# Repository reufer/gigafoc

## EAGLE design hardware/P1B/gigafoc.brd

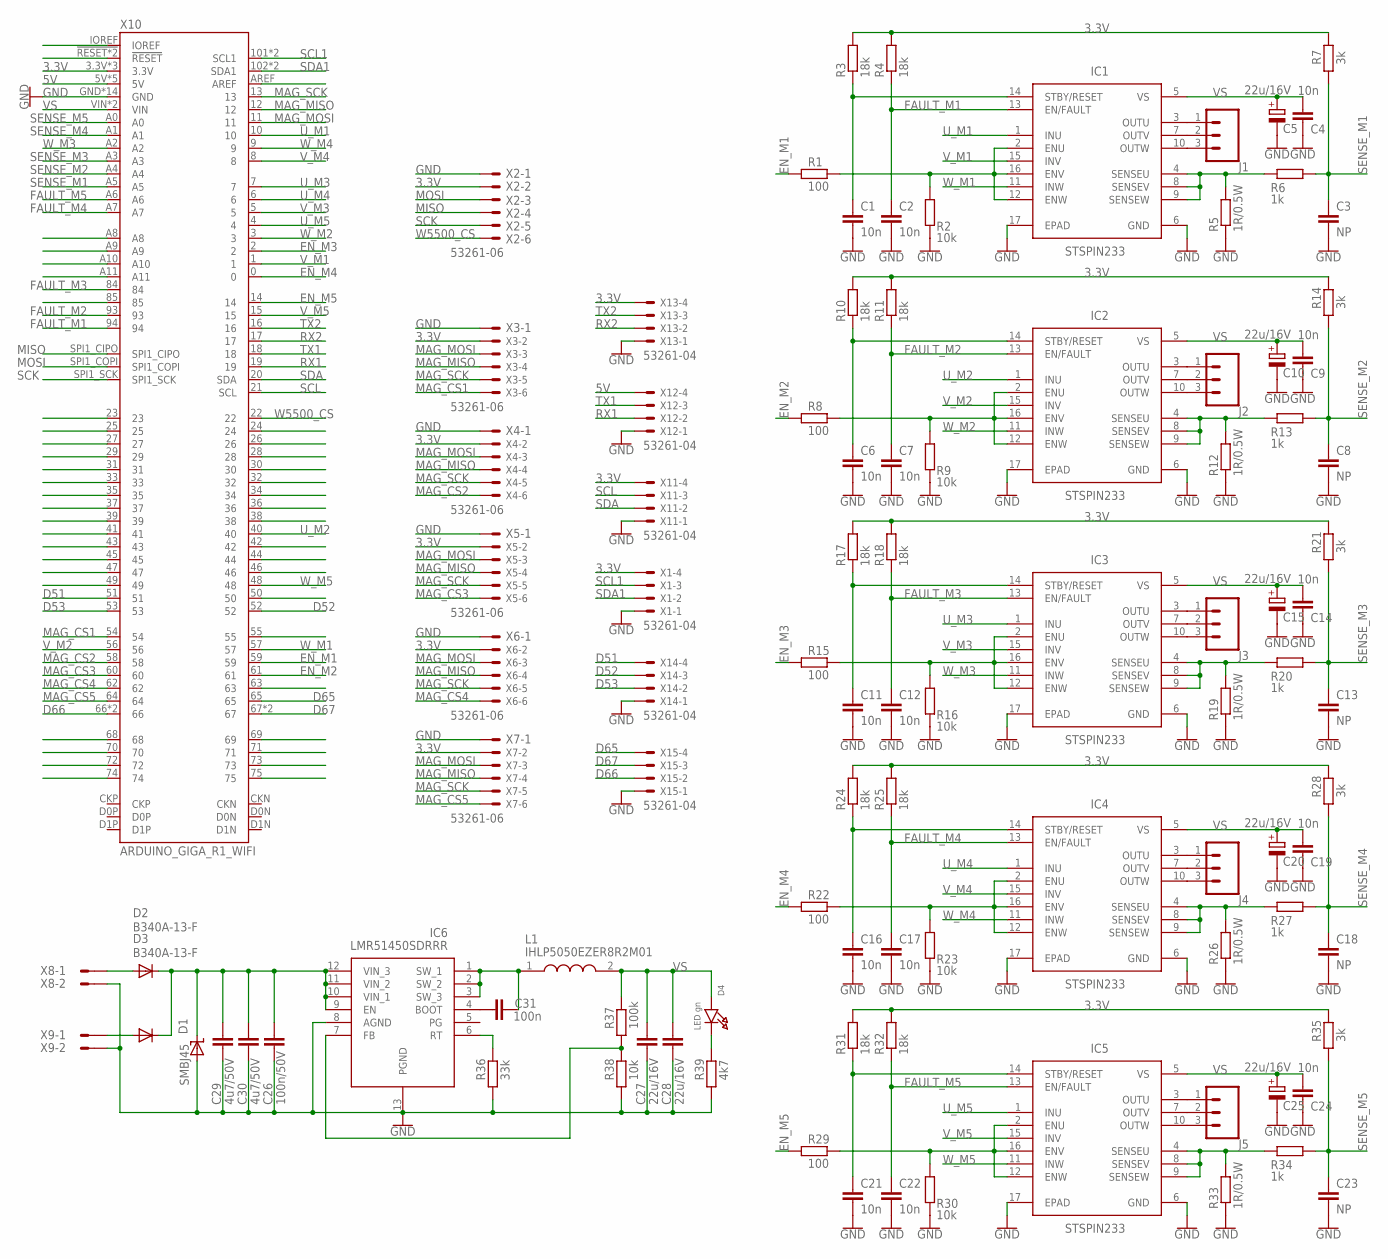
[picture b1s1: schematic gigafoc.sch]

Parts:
C1, C2, C4, C6, C7, C9, C11, C12, C14, C16, C17, C19, C21, C22, C24: 10n; C0603
C3, C8, C13, C18, C23: NP; C0603
C5, C10, C15, C20, C25: 22u/16V; SMC_B
C26: 100n/50V; C0805
C27, C28: 22u/16V; C1210
C29, C30: 4u7/50V; C1210K
C31: 100n; C0603
D1: SMBJ45; SMBJ
D2, D3: B340A-13-F; DO214AC
D4: LED gn; CHIPLED_0603_NOOUTLINE
IC1, IC2, IC3, IC4, IC5: STSPIN233; QFN50P300X300X100-17N
IC6: LMR51450SDRRR; SON50P300X300X80-13N
J1, J2, J3, J4, J5: CONN_03POLAR; MOLEX-1X3
L1: IHLP5050EZER8R2M01; INDPM132129X500N
R1, R8, R15, R22, R29: 100; R0603
R2, R9, R16, R23, R30, R38: 10k; R0603
R3, R4, R10, R11, R17, R18, R24, R25, R31, R32: 18k; R0603
R5, R12, R19, R26, R33: 1R/0.5W; R1206
R6, R13, R20, R27, R34: 1k; R0603
R7, R14, R21, R28, R35: 3k; R0603
R36: 33k; R0603
R37: 100k; R0603
R39: 4k7; R0603
X1, X11, X12, X13, X14, X15: 53261-04
X2, X3, X4, X5, X6, X7: 53261-06
X8, X9: S02P
X10: ARDUINO_GIGA_R1_WIFI; ARDUINO_GIGA_NO_SILK

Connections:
3.3V: R3.2, R4.2, R7.2, R10.2, R11.2, R14.2, R17.2, R18.2, R21.2, R24.2, R25.2, R28.2, R31.2, R32.2, R35.2, X1.4, X2.2, X3.2, X4.2, X5.2, X6.2, X7.2, X10.3.3V, X10.3.3V@1 (3.3V), X10.3.3V@2 (3.3V), X11.4, X13.4
5V: X10.5V, X10.5V@1 (5V), X10.5V@2 (5V), X10.5V@3 (5V), X10.5V@4 (5V), X12.4
24V: D2.A, X8.1
D51: X10.51, X14.4
D52: X10.52, X14.3
D53: X10.53, X14.2
D65: X10.65, X15.4
D66: X10.66, X10.66@1 (66), X15.2
D67: X10.67, X10.67@1 (67), X15.3
EN_M1: R1.1, X10.59
EN_M2: R8.1, X10.61
EN_M3: R15.1, X10.2
EN_M4: R22.1, X10.0
EN_M5: R29.1, X10.14
FAULT_M1: C2.2, IC1.13 (EN/FAULT), R4.1, X10.94
FAULT_M2: C7.2, IC2.13 (EN/FAULT), R11.1, X10.93
FAULT_M3: C12.2, IC3.13 (EN/FAULT), R18.1, X10.84
FAULT_M4: C17.2, IC4.13 (EN/FAULT), R25.1, X10.A7
FAULT_M5: C22.2, IC5.13 (EN/FAULT), R32.1, X10.A6
GND: C1.1, C2.1, C3.1, C4.1, C5.-, C6.1, C7.1, C8.1, C9.1, C10.-, C11.1, C12.1, C13.1, C14.1, C15.-, C16.1, C17.1, C18.1, C19.1, C20.-, C21.1, C22.1, C23.1, C24.1, C25.-, C26.2, C27.2, C28.2, C29.2, C30.2, D1.A, IC1.6 (GND), IC1.17 (EPAD), IC2.6 (GND), IC2.17 (EPAD), IC3.6 (GND), IC3.17 (EPAD), IC4.6 (GND), IC4.17 (EPAD), IC5.6 (GND), IC5.17 (EPAD), IC6.8 (AGND), IC6.13 (PGND), R2.1, R5.1, R9.1, R12.1, R16.1, R19.1, R23.1, R26.1, R30.1, R33.1, R36.1, R38.1, R39.1, X1.1, X2.1, X3.1, X4.1, X5.1, X6.1, X7.1, X8.2, X9.2, X10.GND, X10.GND@1 (GND), X10.GND@2 (GND), X10.GND@3 (GND), X10.GND@4 (GND), X10.GND@5 (GND), X10.GND@6 (GND), X10.GND@7 (GND), X10.GND@8 (GND), X10.GND@9 (GND), X10.GND@10 (GND), X10.GND@11 (GND), X10.GND@12 (GND), X10.GND@13 (GND), X11.1, X12.1, X13.1, X14.1, X15.1
MAG_CS1: X3.6, X10.54
MAG_CS2: X4.6, X10.58
MAG_CS3: X5.6, X10.60
MAG_CS4: X6.6, X10.62
MAG_CS5: X7.6, X10.64
MAG_MISO: X3.4, X4.4, X5.4, X6.4, X7.4, X10.12
MAG_MOSI: X3.3, X4.3, X5.3, X6.3, X7.3, X10.11
MAG_SCK: X3.5, X4.5, X5.5, X6.5, X7.5, X10.13
MISO: X2.4, X10.SPI1_CIPO
MOSI: X2.3, X10.SPI1_COPI
unnamed: IC1.2 (ENU), IC1.12 (ENW), IC1.16 (ENV), R1.2, R2.2
unnamed: C1.2, IC1.14 (STBY/RESET), R3.1
unnamed: IC1.4 (SENSEU), IC1.8 (SENSEV), IC1.9 (SENSEW), R5.2, R6.1
unnamed: C31.1, IC6.4 (BOOT)
unnamed: C31.2, IC6.1 (SW_1), IC6.2 (SW_2), IC6.3 (SW_3), L1.1
unnamed: IC1.3 (OUTU), J1.1
unnamed: IC1.7 (OUTV), J1.2
unnamed: IC1.10 (OUTW), J1.3
unnamed: D4.C, R39.2
unnamed: D3.A, X9.1
unnamed: IC6.7 (FB), R37.1, R38.2
unnamed: IC6.6 (RT), R36.2
unnamed: IC2.2 (ENU), IC2.12 (ENW), IC2.16 (ENV), R8.2, R9.2
unnamed: C6.2, IC2.14 (STBY/RESET), R10.1
unnamed: IC2.4 (SENSEU), IC2.8 (SENSEV), IC2.9 (SENSEW), R12.2, R13.1
unnamed: IC2.3 (OUTU), J2.1
unnamed: IC2.7 (OUTV), J2.2
unnamed: IC2.10 (OUTW), J2.3
unnamed: IC3.2 (ENU), IC3.12 (ENW), IC3.16 (ENV), R15.2, R16.2
unnamed: C11.2, IC3.14 (STBY/RESET), R17.1
unnamed: IC3.4 (SENSEU), IC3.8 (SENSEV), IC3.9 (SENSEW), R19.2, R20.1
unnamed: X10.!RESET, X10.RESET (!RESET)
unnamed: IC3.3 (OUTU), J3.1
unnamed: IC3.7 (OUTV), J3.2
unnamed: IC3.10 (OUTW), J3.3
unnamed: IC4.2 (ENU), IC4.12 (ENW), IC4.16 (ENV), R22.2, R23.2
unnamed: C16.2, IC4.14 (STBY/RESET), R24.1
unnamed: IC4.4 (SENSEU), IC4.8 (SENSEV), IC4.9 (SENSEW), R26.2, R27.1
unnamed: IC4.3 (OUTU), J4.1
unnamed: IC4.7 (OUTV), J4.2
unnamed: IC4.10 (OUTW), J4.3
unnamed: IC5.2 (ENU), IC5.12 (ENW), IC5.16 (ENV), R29.2, R30.2
unnamed: C21.2, IC5.14 (STBY/RESET), R31.1
unnamed: IC5.4 (SENSEU), IC5.8 (SENSEV), IC5.9 (SENSEW), R33.2, R34.1
unnamed: IC5.3 (OUTU), J5.1
unnamed: IC5.7 (OUTV), J5.2
unnamed: IC5.10 (OUTW), J5.3
RX1: X10.19, X12.2
RX2: X10.17, X13.2
SCK: X2.5, X10.SPI1_SCK
SCL: X10.21 (SCL), X11.3
SCL1: X1.3, X10.101 (SCL1), X10.101@1 (SCL1)
SDA: X10.20 (SDA), X11.2
SDA1: X1.2, X10.102 (SDA1), X10.102@1 (SDA1)
SENSE_M1: C3.2, R6.2, R7.1, X10.A5
SENSE_M2: C8.2, R13.2, R14.1, X10.A4
SENSE_M3: C13.2, R20.2, R21.1, X10.A3
SENSE_M4: C18.2, R27.2, R28.1, X10.A1
SENSE_M5: C23.2, R34.2, R35.1, X10.A0
TX1: X10.18, X12.3
TX2: X10.16, X13.3
U_M1: IC1.1 (INU), X10.10
U_M2: IC2.1 (INU), X10.40
U_M3: IC3.1 (INU), X10.7
U_M4: IC4.1 (INU), X10.6
U_M5: IC5.1 (INU), X10.4
VIN: C26.1, C29.1, C30.1, D1.C, D2.C, D3.C, IC6.9 (EN), IC6.10 (VIN_1), IC6.11 (VIN_2), IC6.12 (VIN_3)
VS: C4.2, C5.+, C9.2, C10.+, C14.2, C15.+, C19.2, C20.+, C24.2, C25.+, C27.1, C28.1, D4.A, IC1.5 (VS), IC2.5 (VS), IC3.5 (VS), IC4.5 (VS), IC5.5 (VS), L1.2, R37.2, X10.VIN, X10.VIN@1 (VIN)
V_M1: IC1.15 (INV), X10.1
V_M2: IC2.15 (INV), X10.56
V_M3: IC3.15 (INV), X10.5
V_M4: IC4.15 (INV), X10.8
V_M5: IC5.15 (INV), X10.15
W5500_CS: X2.6, X10.22
W_M1: IC1.11 (INW), X10.57
W_M2: IC2.11 (INW), X10.3
W_M3: IC3.11 (INW), X10.A2
W_M4: IC4.11 (INW), X10.9
W_M5: IC5.11 (INW), X10.48

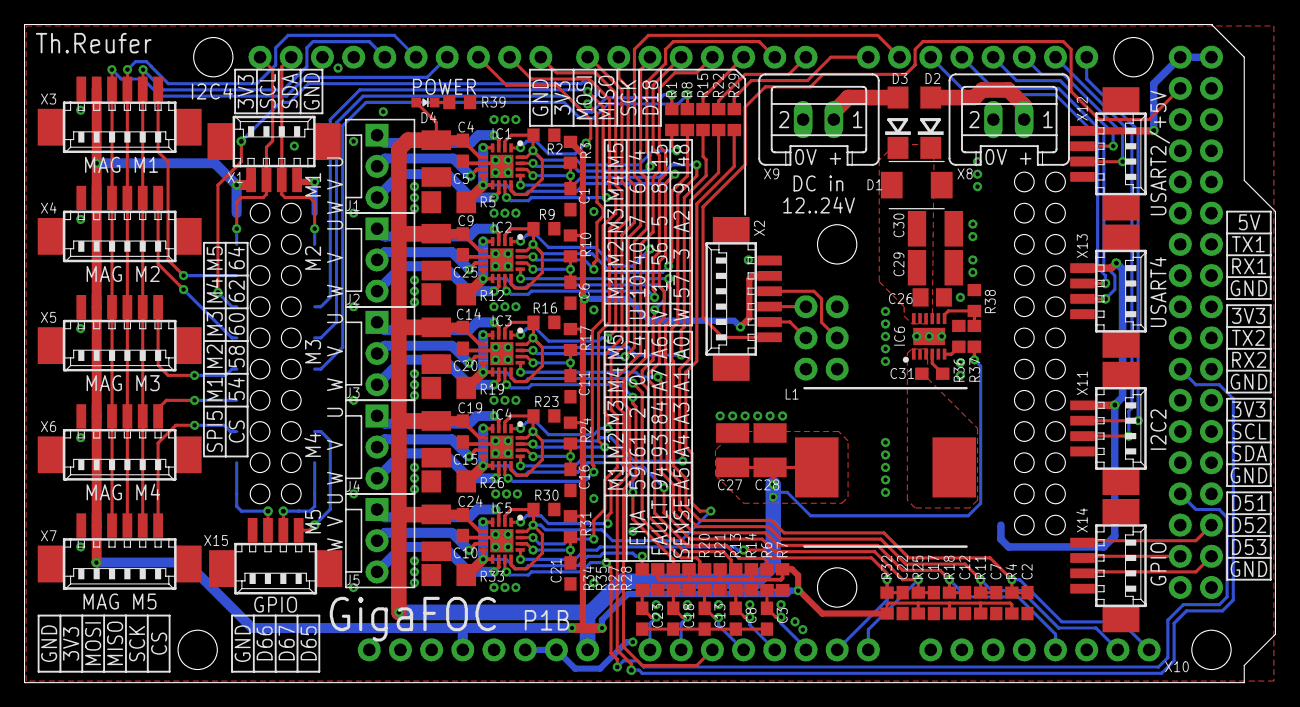
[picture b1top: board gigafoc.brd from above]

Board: 2 copper layers, 101.9 x 53.6 mm, 101 parts (0 on the bottom side), 99 nets.

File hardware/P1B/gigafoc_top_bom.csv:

Comment,Designator,Footprint,LCSC Part #
1R/0.5W,R5 R12 R19 R26 R33,R1206,C880596
3k,R7 R14 R21 R28 R35,R0603,C4211
4k7,R39,R0603,C23162
4u7/50V,C29 C30,C1210K,C880822
10k,R2 R9 R16 R23 R30 R38,R0603,C25804
10n,C1 C2 C4 C6 C7 C9 C11 C12 C14 C16 C17 C19 C21 C22 C24,C0603,C57112
18k,R3 R4 R10 R11 R17 R18 R24 R25 R31 R32,R0603,C25810
22u/16V,C5 C10 C15 C20 C25,SMC_B,C55530
22u/16V,C27 C28,C1210,C2180585
33k,R36,R0603,C4216
100,R1 R8 R15 R22 R29,R0603,C5123610
100k,R37,R0603,C25803
100n,C31,C0603,C57112
100n/50V,C26,C0805,C710626
1k,R6 R13 R20 R27 R34,R0603,C21190
53261-04,X1 X11 X12 X13 X14 X15,53261-04,C696092
53261-06,X2 X3 X4 X5 X6 X7,53261-06,C17393620
B340A-13-F,D2 D3,DO214AC,C85098
IHLP5050EZER8R2M01,L1,INDPM132129X500N,C845094
LED gn,D4,CHIPLED_0603_NOOUTLINE,C12624
LMR51450SDRRR,IC6,SON50P300X300X80-13N,C6890985
SMBJ45,D1,SMBJ,C440304
STSPIN233,IC1 IC2 IC3 IC4 IC5,QFN50P300X300X100-17N,C2653468

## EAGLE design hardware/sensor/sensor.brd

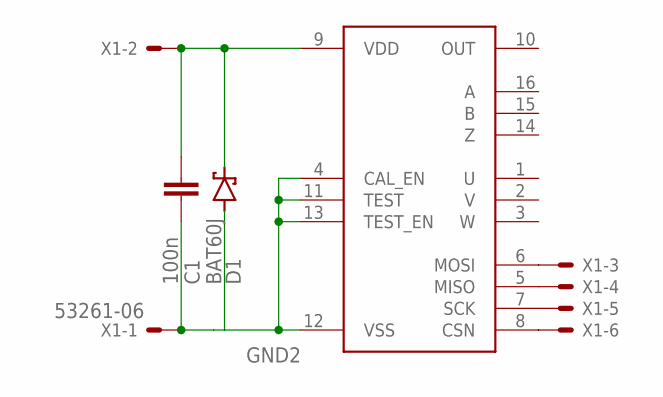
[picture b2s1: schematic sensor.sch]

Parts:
C1: 100n; C0603
D1: BAT60J; SOD323_ST
IC1: MT6835; TSSOP-16
X1: 53261-06

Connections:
GND2: C1.2, D1.A, IC1.4 (CAL_EN), IC1.11 (TEST), IC1.12 (VSS), IC1.13 (TEST_EN), X1.1
unnamed: IC1.5 (MISO), X1.4
unnamed: IC1.7 (SCK), X1.5
unnamed: IC1.8 (CSN), X1.6
unnamed: IC1.6 (MOSI), X1.3
unnamed: C1.1, D1.C, IC1.9 (VDD), X1.2

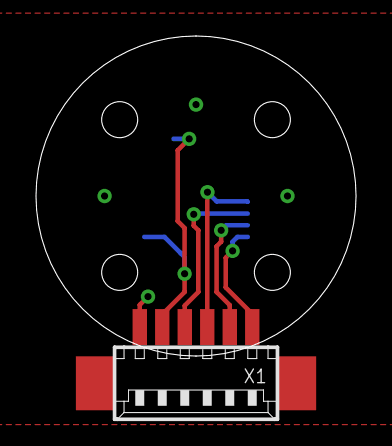
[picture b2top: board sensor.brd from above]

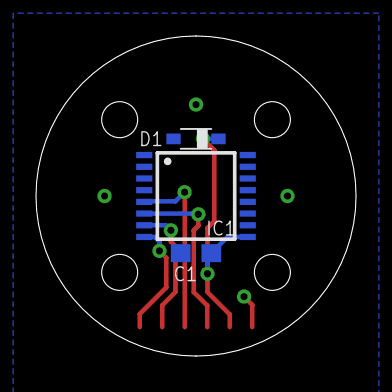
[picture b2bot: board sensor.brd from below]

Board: 2 copper layers, 17.8 x 17.8 mm, 4 parts (3 on the bottom side), 6 nets.

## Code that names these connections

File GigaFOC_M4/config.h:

#pragma once

#include <PinNames.h>

#define HARDWARE_P1A
//#define HARDWARE_P1B

#define MOTOR_2204

//#define SENSOR_MT6701
#define SENSOR_MT6835

#define DRIVER_MBED
//#define DRIVER_PORTENTA
//#define DRIVER_STM32

#define MOTORS 5

#define MOTOR_PP 7
#define MOTOR_KV NOT_SET
#define MOTOR_L NOT_SET
#define MOTOR_R NOT_SET

#ifdef MOTOR_2204
#define MOTOR_PP 7
#define MOTOR_KV 260.0f
#define MOTOR_L 0.00173f
#define MOTOR_R 10.0f
#endif

#define VOLTAGE_POWER_SUPPLY 9
#define VOLTAGE_SENSOR_ALIGN 3
#define VELOCITY_INDEX_SEARCH 3

// Hardware P1A
#ifdef HARDWARE_P1A
#define PIN_U_M1    D10 // PK1_ALT1
#define PIN_V_M1    D1  // PA9_ALT1
#define PIN_W_M1    D57 // PJ9_ALT1

#define PIN_U_M2    D85 // PA5
#define PIN_V_M2    D66 // PA1
#define PIN_W_M2    D3  // PA2

#define PIN_U_M3    D7  // PB4
#define PIN_V_M3    D5  // PA7_ALT1
#define PIN_W_M3    A2  // PB0_ALT1

#define PIN_U_M4    D6  // PD13
#define PIN_V_M4    D8  // PB8
#define PIN_W_M4    D9  // PB9

#define PIN_U_M5    D4  // PJ8_ALT1
#define PIN_V_M5    D15 // PC7_ALT1
#define PIN_W_M5    D48 // PK0_ALT1

#define PIN_EN_M1   D2
#define PIN_EN_M2   D14
#define PIN_EN_M3   D0
#define PIN_EN_M4   D16
#define PIN_EN_M5   D17

#define PIN_MAG_CS1 D56
#define PIN_MAG_CS2 D58
#define PIN_MAG_CS3 D60
#define PIN_MAG_CS4 D62
#define PIN_MAG_CS5 D64

#define PIN_SENSE_M1 A5
#define PIN_SENSE_M2 A4
#define PIN_SENSE_M3 A3
#define PIN_SENSE_M4 A1
#define PIN_SENSE_M5 A0

#define PIN_FAULT_M1 D94
#define PIN_FAULT_M2 D93
#define PIN_FAULT_M3 D84
#define PIN_FAULT_M4 A7
#define PIN_FAULT_M5 A6
#endif

// Hardware P1B
#ifdef HARDWARE_P1B
#define PIN_U_M1    D10 // PK1_ALT1
#define PIN_V_M1    D1  // PA9_ALT1
#define PIN_W_M1    D57 // PJ9_ALT1

#define PIN_U_M2    D40 // PE6
#define PIN_V_M2    D56 // PA6
#define PIN_W_M2    D3  // PA2

#define PIN_U_M3    D7  // PB4
#define PIN_V_M3    D5  // PA7_ALT1
#define PIN_W_M3    A2  // PB0_ALT1

#define PIN_U_M4    D6  // PD13
#define PIN_V_M4    D8  // PB8
#define PIN_W_M4    D9  // PB9

#define PIN_U_M5    D4  // PJ8_ALT1
#define PIN_V_M5    D15 // PC7_ALT1
#define PIN_W_M5    D48 // PK0_ALT1

#define PIN_EN_M1   D59
#define PIN_EN_M2   D61
#define PIN_EN_M3   D2
#define PIN_EN_M4   D0
#define PIN_EN_M5   D14

#define PIN_MAG_CS1 D54
#define PIN_MAG_CS2 D58
#define PIN_MAG_CS3 D60
#define PIN_MAG_CS4 D62
#define PIN_MAG_CS5 D64

#define PIN_SENSE_M1 A5
#define PIN_SENSE_M2 A4
#define PIN_SENSE_M3 A3
#define PIN_SENSE_M4 A1
#define PIN_SENSE_M5 A0

#define PIN_FAULT_M1 D94
#define PIN_FAULT_M2 D93
#define PIN_FAULT_M3 D84
#define PIN_FAULT_M4 A7
#define PIN_FAULT_M5 A6
#endif

// SPI1
#define MAG_SPI SPI1
#define PIN_SPI_MOSI D11
#define PIN_SPI_MISO D12
#define PIN_SPI_SCK  D13

#define PIN_LED D88

const PinMap PinMap_TIM[] = {
  { PK_1,  TIM1_BASE,  STM_PIN_DATA_EXT(STM_MODE_AF_PP, GPIO_PULLUP, GPIO_AF1_TIM1, 1, 0)}, // TIM1_CH1
  { PA_9,  TIM1_BASE,  STM_PIN_DATA_EXT(STM_MODE_AF_PP, GPIO_PULLUP, GPIO_AF1_TIM1, 2, 0)}, // TIM1_CH2
  { PJ_9,  TIM1_BASE,  STM_PIN_DATA_EXT(STM_MODE_AF_PP, GPIO_PULLUP, GPIO_AF1_TIM1, 3, 0)}, // TIM1_CH3

  { PA_5,  TIM2_BASE,  STM_PIN_DATA_EXT(STM_MODE_AF_PP, GPIO_PULLUP, GPIO_AF1_TIM2, 1, 0)}, // TIM2_CH1
  { PA_1,  TIM2_BASE,  STM_PIN_DATA_EXT(STM_MODE_AF_PP, GPIO_PULLUP, GPIO_AF1_TIM2, 2, 0)}, // TIM2_CH2
  { PA_2,  TIM2_BASE,  STM_PIN_DATA_EXT(STM_MODE_AF_PP, GPIO_PULLUP, GPIO_AF1_TIM2, 3, 0)}, // TIM2_CH3

  { PB_4,  TIM3_BASE,  STM_PIN_DATA_EXT(STM_MODE_AF_PP, GPIO_PULLUP, GPIO_AF2_TIM3, 1, 0)}, // TIM3_CH1
  { PA_7,  TIM3_BASE,  STM_PIN_DATA_EXT(STM_MODE_AF_PP, GPIO_PULLUP, GPIO_AF2_TIM3, 2, 0)}, // TIM3_CH2
  { PB_0,  TIM3_BASE,  STM_PIN_DATA_EXT(STM_MODE_AF_PP, GPIO_PULLUP, GPIO_AF2_TIM3, 3, 0)}, // TIM3_CH3

  { PD_13, TIM4_BASE,  STM_PIN_DATA_EXT(STM_MODE_AF_PP, GPIO_PULLUP, GPIO_AF2_TIM4, 2, 0)}, // TIM4_CH2
  { PB_8,  TIM4_BASE,  STM_PIN_DATA_EXT(STM_MODE_AF_PP, GPIO_PULLUP, GPIO_AF2_TIM4, 3, 0)}, // TIM4_CH3
  { PB_9,  TIM4_BASE,  STM_PIN_DATA_EXT(STM_MODE_AF_PP, GPIO_PULLUP, GPIO_AF2_TIM4, 4, 0)}, // TIM4_CH4

  { PJ_8,  TIM8_BASE,  STM_PIN_DATA_EXT(STM_MODE_AF_PP, GPIO_PULLUP, GPIO_AF3_TIM8, 1, 0)}, // TIM8_CH1
  { PC_7,  TIM8_BASE,  STM_PIN_DATA_EXT(STM_MODE_AF_PP, GPIO_PULLUP, GPIO_AF3_TIM8, 2, 0)}, // TIM8_CH2
  { PK_0,  TIM8_BASE,  STM_PIN_DATA_EXT(STM_MODE_AF_PP, GPIO_PULLUP, GPIO_AF3_TIM8, 3, 0)}, // TIM8_CH3
  { NC, NC, 0}
};


// https://github.com/arduino/mbed-os/blob/extrapatches-6.17.0/targets/TARGET_STM/TARGET_STM32H7/TARGET_STM32H747xI/TARGET_GIGA/PeripheralPins.c
// TIM5 cannot be used because already used by the us_ticker
// TIM2 cannot be used because already used by the us_ticker (DUAL_CORE)
const PinMap PinMap_PWM[] = {
  { PK_1,  PWM_1,  STM_PIN_DATA_EXT(STM_MODE_AF_PP, GPIO_NOPULL, GPIO_AF1_TIM1,  1, 0)}, // TIM1_CH1 - 1.1
  { PA_9,  PWM_1,  STM_PIN_DATA_EXT(STM_MODE_AF_PP, GPIO_NOPULL, GPIO_AF1_TIM1,  2, 0)}, // TIM1_CH2 - 1.2
  { PJ_9,  PWM_1,  STM_PIN_DATA_EXT(STM_MODE_AF_PP, GPIO_NOPULL, GPIO_AF1_TIM1,  3, 0)}, // TIM1_CH3 - 1.3

  { PE_6,  PWM_15, STM_PIN_DATA_EXT(STM_MODE_AF_PP, GPIO_NOPULL, GPIO_AF4_TIM15, 2, 0)}, // TIM15_CH2 - 2.1
  { PA_6,  PWM_13, STM_PIN_DATA_EXT(STM_MODE_AF_PP, GPIO_NOPULL, GPIO_AF9_TIM13, 1, 0)}, // TIM13_CH1 - 2.2
  { PA_2,  PWM_15, STM_PIN_DATA_EXT(STM_MODE_AF_PP, GPIO_NOPULL, GPIO_AF4_TIM15, 1, 0)}, // TIM15_CH1 - 2.3

  { PB_4,  PWM_3,  STM_PIN_DATA_EXT(STM_MODE_AF_PP, GPIO_NOPULL, GPIO_AF2_TIM3,  1, 0)}, // TIM3_CH1 - 3.1
  { PA_7,  PWM_3,  STM_PIN_DATA_EXT(STM_MODE_AF_PP, GPIO_NOPULL, GPIO_AF2_TIM3,  2, 0)}, // TIM3_CH2 - 3.2
  { PB_0,  PWM_3,  STM_PIN_DATA_EXT(STM_MODE_AF_PP, GPIO_NOPULL, GPIO_AF2_TIM3,  3, 0)}, // TIM3_CH3 - 3.3

  { PD_13, PWM_4,  STM_PIN_DATA_EXT(STM_MODE_AF_PP, GPIO_NOPULL, GPIO_AF2_TIM4,  2, 0)}, // TIM4_CH2 - 4.1
  { PB_8,  PWM_4,  STM_PIN_DATA_EXT(STM_MODE_AF_PP, GPIO_NOPULL, GPIO_AF2_TIM4,  3, 0)}, // TIM4_CH3 - 4.2
  { PB_9,  PWM_4,  STM_PIN_DATA_EXT(STM_MODE_AF_PP, GPIO_NOPULL, GPIO_AF2_TIM4,  4, 0)}, // TIM4_CH4 - 4.3

  { PJ_8,  PWM_8,  STM_PIN_DATA_EXT(STM_MODE_AF_PP, GPIO_NOPULL, GPIO_AF3_TIM8,  1, 0)}, // TIM8_CH1 - 5.1
  { PC_7,  PWM_8,  STM_PIN_DATA_EXT(STM_MODE_AF_PP, GPIO_NOPULL, GPIO_AF3_TIM8,  2, 0)}, // TIM8_CH2 - 5.2
  { PK_0,  PWM_8,  STM_PIN_DATA_EXT(STM_MODE_AF_PP, GPIO_NOPULL, GPIO_AF3_TIM8,  3, 0)}, // TIM8_CH3 - 5.3

  { PB_14_ALT1, PWM_12, STM_PIN_DATA_EXT(STM_MODE_AF_PP, GPIO_NOPULL, GPIO_AF2_TIM12, 1, 0)}, // TIM12_CH1
  { PB_15_ALT1, PWM_12, STM_PIN_DATA_EXT(STM_MODE_AF_PP, GPIO_NOPULL, GPIO_AF2_TIM12, 2, 0)}, // TIM12_CH2
  { PF_8,       PWM_13, STM_PIN_DATA_EXT(STM_MODE_AF_PP, GPIO_NOPULL, GPIO_AF9_TIM13, 1, 0)}, // TIM13_CH1
  { PF_9,       PWM_14, STM_PIN_DATA_EXT(STM_MODE_AF_PP, GPIO_NOPULL, GPIO_AF9_TIM14, 1, 0)}, // TIM14_CH1
  { PH_6,       PWM_12, STM_PIN_DATA_EXT(STM_MODE_AF_PP, GPIO_NOPULL, GPIO_AF2_TIM12, 1, 0)}, // TIM12_CH1 D13
  { PH_9,       PWM_12, STM_PIN_DATA_EXT(STM_MODE_AF_PP, GPIO_NOPULL, GPIO_AF2_TIM12, 2, 0)}, // TIM12_CH2 D65
  { PE_5,       PWM_15, STM_PIN_DATA_EXT(STM_MODE_AF_PP, GPIO_NOPULL, GPIO_AF4_TIM15, 1, 0)}, // TIM15_CH1 D51
  { PA_1,       PWM_15, STM_PIN_DATA_EXT(STM_MODE_AF_PP, GPIO_NOPULL, GPIO_AF4_TIM15, 1, 1)}, // TIM15_CH1N
  { PA_3,       PWM_15, STM_PIN_DATA_EXT(STM_MODE_AF_PP, GPIO_NOPULL, GPIO_AF4_TIM15, 2, 0)}, // TIM15_CH2 D2
  { PB_6_ALT0,  PWM_16, STM_PIN_DATA_EXT(STM_MODE_AF_PP, GPIO_NOPULL, GPIO_AF1_TIM16, 1, 1)}, // TIM16_CH1N
  { PB_7_ALT0,  PWM_17, STM_PIN_DATA_EXT(STM_MODE_AF_PP, GPIO_NOPULL, GPIO_AF1_TIM17, 1, 1)}, // TIM17_CH1N
  { PE_4,       PWM_15, STM_PIN_DATA_EXT(STM_MODE_AF_PP, GPIO_NOPULL, GPIO_AF4_TIM15, 1, 1)}, // TIM15_CH1N
  { PF_6,       PWM_16, STM_PIN_DATA_EXT(STM_MODE_AF_PP, GPIO_NOPULL, GPIO_AF1_TIM16, 1, 0)}, // TIM16_CH1
  { PF_7,       PWM_17, STM_PIN_DATA_EXT(STM_MODE_AF_PP, GPIO_NOPULL, GPIO_AF1_TIM17, 1, 0)}, // TIM17_CH1
  { PF_8_ALT0,  PWM_16, STM_PIN_DATA_EXT(STM_MODE_AF_PP, GPIO_NOPULL, GPIO_AF1_TIM16, 1, 1)}, // TIM16_CH1N
  { PF_9_ALT0,  PWM_17, STM_PIN_DATA_EXT(STM_MODE_AF_PP, GPIO_NOPULL, GPIO_AF1_TIM17, 1, 1)}, // TIM17_CH1N
  { NC, NC, 0}
};

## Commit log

2024-08-08 snapshot
2024-08-08 - new P1B hardware - MT6835 sensor PCB

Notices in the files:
parts and their libraries:
SparkFun-Boards: Licensing: Creative Commons ShareAlike 4.0 International - https://creativecommons.org/licenses/by-sa/4.0
microbuilder: This work is placed in the public domain, and may be freely used for commercial and non-commercial work with the following conditions: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
